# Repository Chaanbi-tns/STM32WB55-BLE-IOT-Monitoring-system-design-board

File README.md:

# 🌐 STM32WB55 BLE & IoT Monitoring System Design Board

> Carte de monitoring IoT sans fil bicoeur (Cortex-M4 + Cortex-M0+) propulsée par le microcontrôleur **STM32WB55**, conçue pour l'acquisition de données et la transmission BLE (Bluetooth Low Energy).

---

## 📋 Table des matières
- [Aperçu du projet](#-aperçu-du-projet)
- [Fonctionnalités principales](#-fonctionnalités-principales)
- [Arborescence du projet](#-arborescence-du-projet)
- [Structure du matériel (KiCad)](#-structure-du-matériel-kicad)
- [Guide de démarrage rapide](#-guide-de-démarrage-rapide)
- [Auteur](#-auteur)

---

## 🚀 Aperçu du projet
Ce projet consiste en la conception complète d'une carte électronique dédiée au monitoring IoT. Basée sur le SoC sans fil **STM32WB55**, elle associe des performances de calcul et une connectivité radio basse consommation (Bluetooth 5.0).

---

## ✨ Fonctionnalités principales
- **Microcontrôleur principal :** STM32WB55xx (Dual-Core : ARM Cortex-M4 pour l'application & Cortex-M0+ pour la pile Bluetooth).
- **Connectivité :** Bluetooth Low Energy (BLE).
- **Conception CAO :** Réalisé sous **KiCad** (schéma, routage PCB, empreintes et bibliothèques personnalisées).

---

## 📂 Arborescence du projet
Voici l'organisation des fichiers de ce dépôt[cite: 1] :

```tree
STM32WB_BLE/
├── Docs/                       # Documentation, datasheets et notes techniques
├── DFL_Library.pretty/         # Empreintes KiCad personnalisées
├── DFL_Library.kicad_sym       # Symboles schématiques personnalisés
├── STM32WB_BLE.kicad_pro       # Fichier projet KiCad principal
├── STM32WB_BLE.kicad_sch       # Schéma électronique
├── STM32WB_BLE.kicad_pcb       # Routage du PCB
├── STM32WB_BLE.csv             # Nomenclature (BOM)
└── .history/                   # Historique et versions de conception

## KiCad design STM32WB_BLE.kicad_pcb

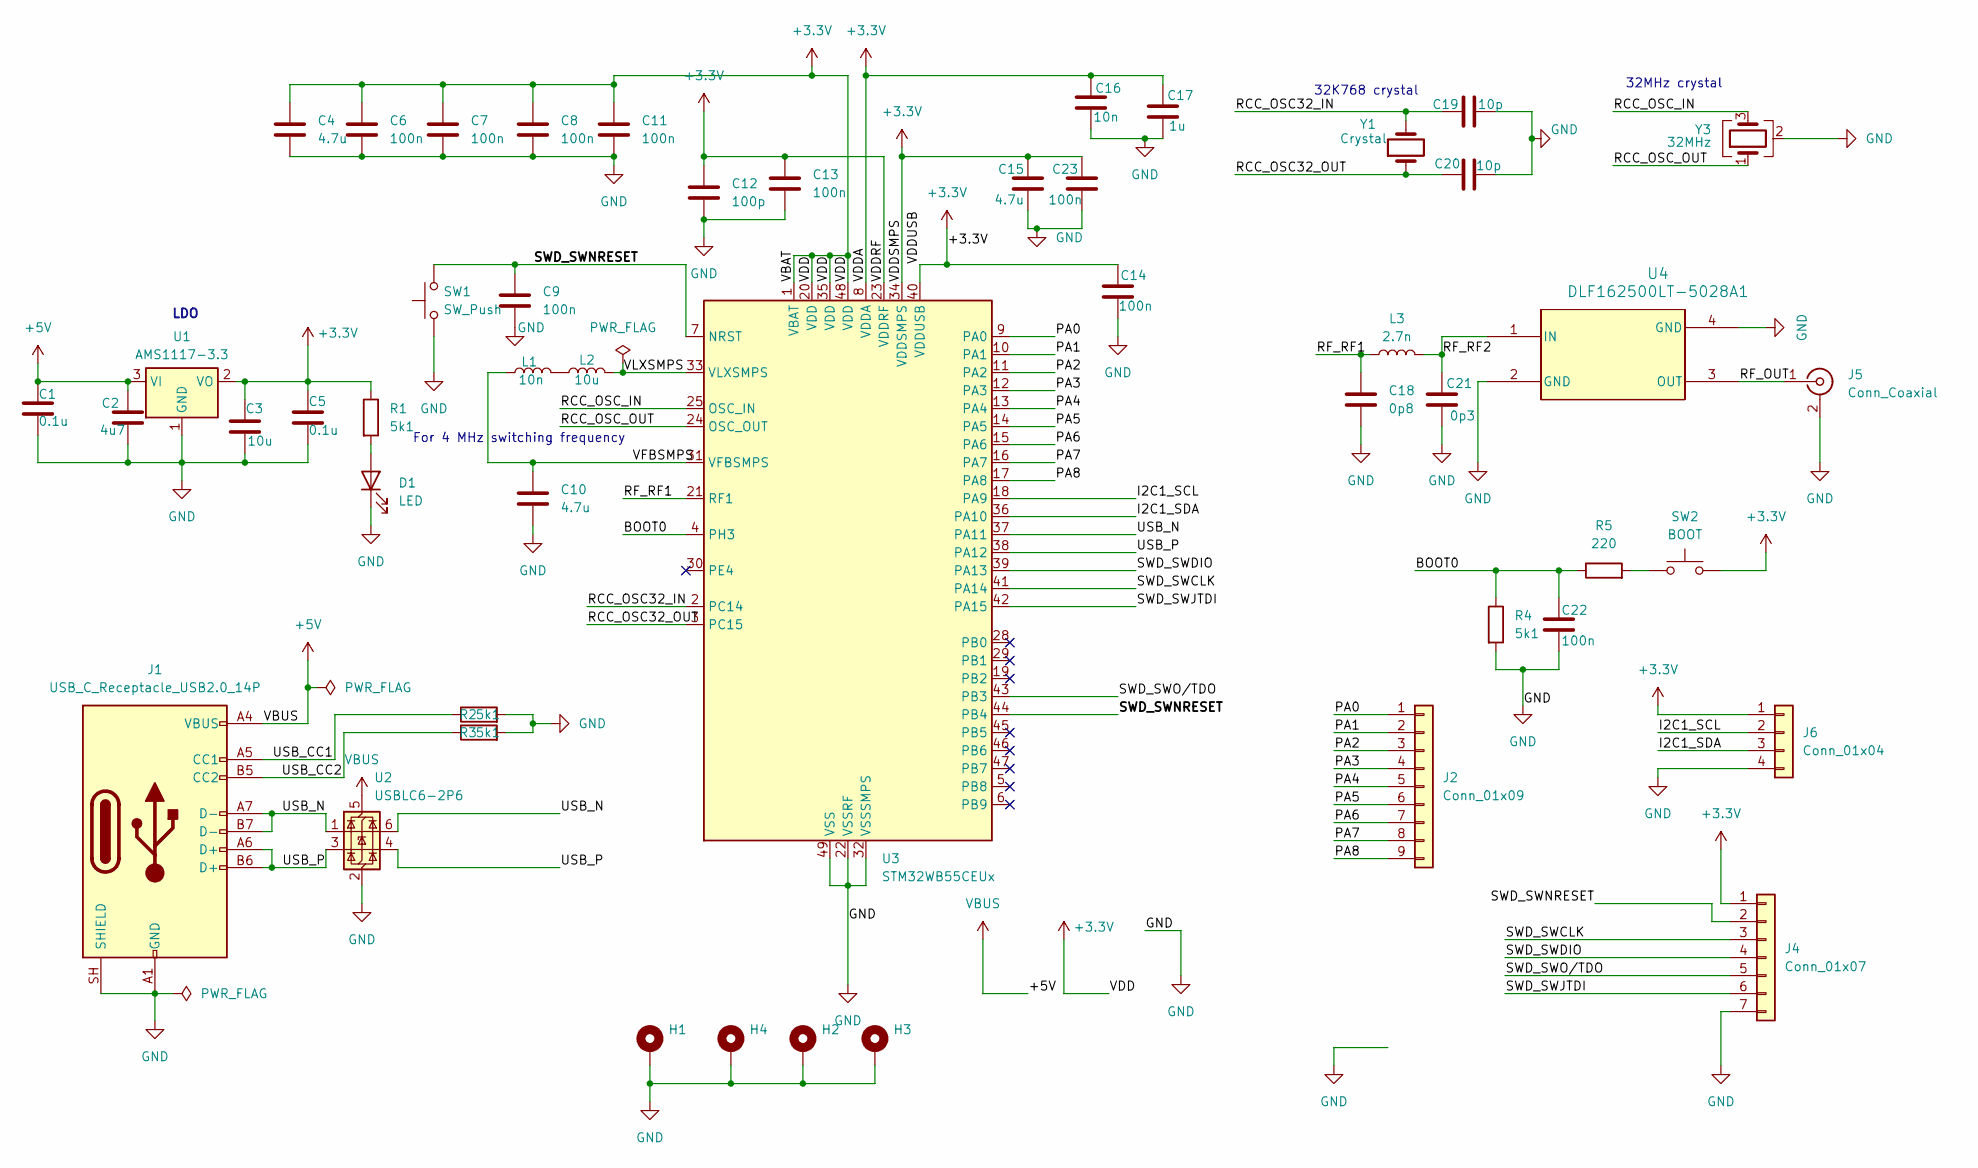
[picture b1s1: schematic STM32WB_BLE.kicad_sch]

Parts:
C1, C5: 0.1u; C_0805_2012Metric
C2: 4u7; C_0805_2012Metric
C3: 10u; C_0805_2012Metric
C4, C10, C15: 4.7u; C_0805_2012Metric
C6, C7, C8, C9, C11, C13, C14, C23: 100n; C_0805_2012Metric
C12: 100p; C_0402_1005Metric
C16: 10n; C_0805_2012Metric
C17: 1u; C_0805_2012Metric
C18: 0p8; C_0402_1005Metric
C19, C20: 10p; C_0402_1005Metric
C21: 0p3; C_0402_1005Metric
C22: 100n; C_0603_1608Metric
D1: LED; LED_0603_1608Metric
H1, H2, H3, H4: MountingHole_Pad; MountingHole_2.5mm_Pad_Via
J1: USB_C_Receptacle_USB2.0_14P; USB_C_Receptacle_HRO_TYPE-C-31-M-12
J2: Conn_01x09; JST_EH_B9B-EH-A_1x09_P2.50mm_Vertical
J4: Conn_01x07; JST_EH_B7B-EH-A_1x07_P2.50mm_Vertical
J5: Conn_Coaxial; U.FL_Hirose_U.FL-R-SMT-1_Vertical
J6: Conn_01x04; JST_EH_S4B-EH_1x04_P2.50mm_Horizontal
L1: 10n; L_0402_1005Metric
L2: 10u; L_0805_2012Metric
L3: 2.7n; L_0402_1005Metric
R1, R2, R3, R4: 5k1; R_0805_2012Metric
R5: 220; R_0805_2012Metric
SW1: SW_Push; SW_Push_1P1T_NO_CK_KMR2
SW2: BOOT; SW_Push_1P1T_NO_CK_KMR2
U1: AMS1117-3.3; SOT-223-3_TabPin2
U2: USBLC6-2P6; SOT-666
U3: STM32WB55CEUx; QFN-48-1EP_7x7mm_P0.5mm_EP5.6x5.6mm
U4: DLF162500LT-5028A1; DLF-4_1P6X0P8
Y1: Crystal; Crystal_SMD_2012-2Pin_2.0x1.2mm_HandSoldering
Y3: 32MHz; Crystal_SMD_2016-4Pin_2.0x1.6mm

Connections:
+3.3V: C3.1, C4.1, C5.1, C6.1, C7.1, C8.1, C11.1, C12.1, C13.1, C14.1, C15.1, C16.1, C17.1, C23.1, J4.1, J6.1, R1.1, SW2.2, U1.2 (VO), U3.1 (VBAT), U3.8 (VDDA), U3.20 (VDD), U3.23 (VDDRF), U3.34 (VDDSMPS), U3.35 (VDD), U3.40 (VDDUSB), U3.48 (VDD)
+5V: C1.1, C2.1, J1.A4 (VBUS), J1.A9 (VBUS), J1.B4 (VBUS), J1.B9 (VBUS), U1.3 (VI), U2.5 (VBUS)
/BOOT0: C22.1, R4.1, R5.1, U3.4 (PH3)
/I2C1_SCL: J6.2, U3.18 (PA9)
/I2C1_SDA: J6.3, U3.36 (PA10)
/PA0: J2.1, U3.9 (PA0)
/PA1: J2.2, U3.10 (PA1)
/PA2: J2.3, U3.11 (PA2)
/PA3: J2.4, U3.12 (PA3)
/PA4: J2.5, U3.13 (PA4)
/PA5: J2.6, U3.14 (PA5)
/PA6: J2.7, U3.15 (PA6)
/PA7: J2.8, U3.16 (PA7)
/PA8: J2.9, U3.17 (PA8)
/RCC_OSC32_IN: C19.1, U3.2 (PC14), Y1.2
/RCC_OSC32_OUT: C20.1, U3.3 (PC15), Y1.1
/RCC_OSC_IN: U3.25 (OSC_IN), Y3.3
/RCC_OSC_OUT: U3.24 (OSC_OUT), Y3.1
/RF_OUT: J5.1 (In), U4.3 (OUT)
/RF_RF1: C18.1, L3.1, U3.21 (RF1)
/RF_RF2: C21.1, L3.2, U4.1 (IN)
/SWD_SWCLK: J4.3, U3.41 (PA14)
/SWD_SWDIO: J4.4, U3.39 (PA13)
/SWD_SWJTDI: J4.6, U3.42 (PA15)
/SWD_SWNRESET: C9.1, J4.2, SW1.2, U3.7 (NRST), U3.44 (PB4)
/SWD_SWO/TDO: J4.5, U3.43 (PB3)
/USB_CC1: J1.A5 (CC1), R2.1
/USB_CC2: J1.B5 (CC2), R3.1
/USB_N: J1.A7 (D-), J1.B7 (D-), U2.1 (I/O1), U2.6 (I/O1), U3.37 (PA11)
/USB_P: J1.A6 (D+), J1.B6 (D+), U2.3 (I/O2), U2.4 (I/O2), U3.38 (PA12)
/VFBSMPS: C10.1, L1.1, U3.31 (VFBSMPS)
/VLXSMPS: L2.2, U3.33 (VLXSMPS)
GND: C1.2, C2.2, C3.2, C4.2, C5.2, C6.2, C7.2, C8.2, C9.2, C10.2, C11.2, C12.2, C13.2, C14.2, C15.2, C16.2, C17.2, C18.2, C19.2, C20.2, C21.2, C22.2, C23.2, D1.1 (K), H1.1 (1_1), H2.1 (1_1), H3.1 (1_1), H4.1 (1_1), J1.A1 (GND), J1.A12 (GND), J1.B1 (GND), J1.B12 (GND), J1.SH (SHIELD), J4.7, J5.2 (Ext), J6.4, R2.2, R3.2, R4.2, SW1.1, U1.1 (GND), U2.2 (GND), U3.22 (VSSRF), U3.32 (VSSSMPS), U3.49 (VSS), U4.2 (GND), U4.4 (GND), Y3.2 (G), Y3.4 (G)
unnamed: D1.2 (A), R1.2
unnamed: L1.2, L2.1
unnamed: R5.2, SW2.1

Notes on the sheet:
32K768 crystal
LDO
For 4 MHz switching frequency
32MHz crystal

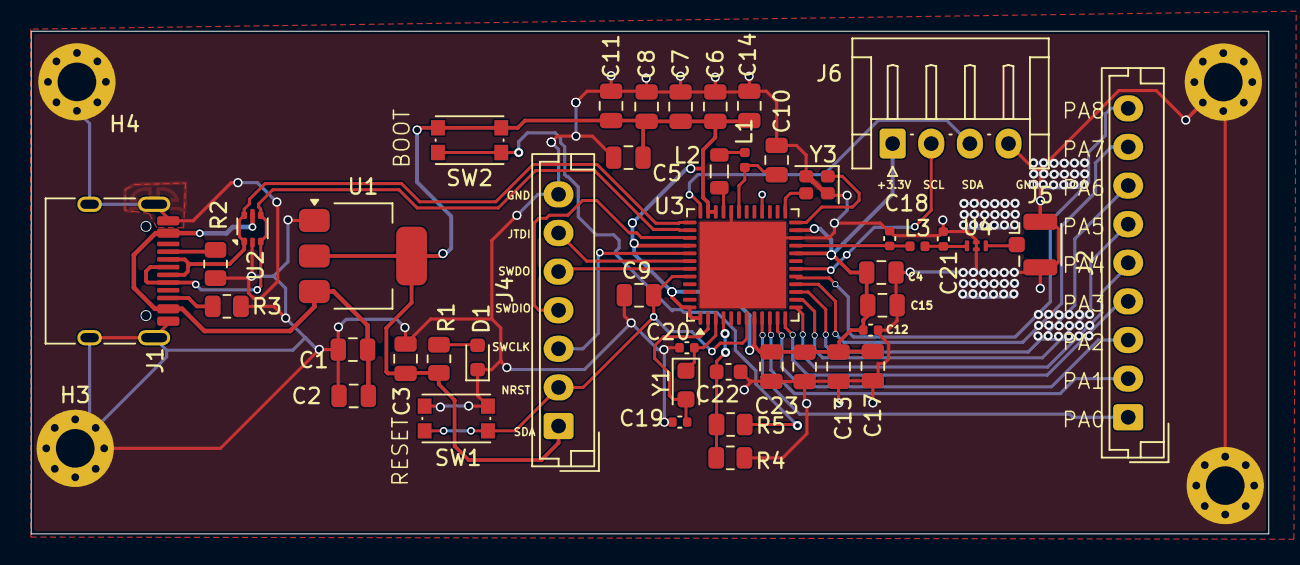
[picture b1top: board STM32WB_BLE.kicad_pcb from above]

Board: 2 copper layers, 80.1 x 32.5 mm, 49 parts (0 on the bottom side), 36 nets.
